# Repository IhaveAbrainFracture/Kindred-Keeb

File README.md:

# Kindred-Keeb
A keyboard themed and designed around the league of legends character Kindred, made for a certain someone <3

# why i made this
So the chronic ado fan this is going to is a keyboard fan and arguably a nerd in all things keyboard related and im not, this project was in part 1. to make a rly good gift but even more 2. to understand keyboards (the in's and the out's) such that when she eventually starts rambling again i can understand all the keyboard things she spews out.

View the full cad here (open in a new tab) : https://cad.onshape.com/documents/49660f55174e9c1ee612018b/w/865d86d8a66051a73309fb28/e/2b79c125cb158cfc9eb8a47f?renderMode=0&leftPanel=false&uiState=687a42a20f797b40055a065f

# Specificaton (Firmware)
1. 3 LAYERS OF FULL CUSTOMISABILITY!!!!!
2. 5 intergrated macros
3. kmk and fully open source

# Specifications (Electronics)
1. Hot swappable (you dont need to get married to the first switch you solder)
2. cool silk layer
3. run by a pico

# Specifications (Mechanical)
1. minimal bolts and others
2. textured arm rest that is magnetically held
3. only 4 major printed parts
4. custom keycaps
5. very thematicaly/lore accurate

# instructions to build
1.using the dowels and such attach the 2 major case and plate parts together then if possible 'melt' then together (like press a iron on both or smthing)

2. in the allocated area insert the insert nuts
   
3.cut and place the foam in the alloacted area then place the pcb on the groves outlines for it

4. place the fully assembled plate ontop of the pcb before placing all the switches
   
5. place the plate pcb sandwitch on the case and bolt into the allocated bolt holes and pray

# BOM 
| Item | Amount | Cost (AUD) | Cost (USD) | Link |
|------|--------|--------------|------------|------|
|Magnets| 50 (i cant order less)  |   $3.32      |        .. | [here](https://www.aliexpress.com/item/1005009515673951.html?spm=a2g0o.productlist.main.3.924e5032RkWiGB&algo_pvid=626def4a-fc6e-4400-b7f1-f96717275f47&algo_exp_id=626def4a-fc6e-4400-b7f1-f96717275f47-2&pdp_ext_f=%7B"order"%3A"-1"%2C"eval"%3A"1"%7D&pdp_npi=4%40dis%21AUD%215.35%213.32%21%21%213.43%212.13%21%402101c5bf17528901380865997ea1e8%2112000049339085641%21sea%21AU%216189345413%21X&curPageLogUid=kPWgozpKm8qq&utparam-url=scene%3Asearch%7Cquery_from%3A)     |
| Stabilisers|  1x   |   9.69           |            |   [Here](https://www.aliexpress.com/item/1005009309795353.html?spm=a2g0o.cart.0.0.75b938dasyPdvw&mp=1&pdp_npi=5%40dis%21AUD%21AUD%2017.62%21AUD%209.69%21%21AUD%209.69%21%21%21%4021010c9a17528903143906876e5d89%2112000048700927954%21ct%21AU%216189345413%21%211%210)   |
|   Akko blue switches   |   45x     |    23.19          |            |   [here](https://www.aliexpress.com/item/1005005514262670.html?spm=a2g0o.cart.0.0.75b938dasyPdvw&mp=1&pdp_npi=5%40dis%21AUD%21AUD%2027.28%21AUD%2023.19%21%21AUD%2023.19%21%21%21%4021010c9a17528903143906876e5d89%2112000033372141692%21ct%21AU%216189345413%21%211%210&pdp_ext_f=%7B"cart2PdpParams"%3A%7B"pdpBusinessMode"%3A"retail"%7D%7D)   |
| Keycaps 132 key purple  |   1x    |     20.61         |            |   [here](https://www.aliexpress.com/item/1005004537134105.html?spm=a2g0o.cart.0.0.3c6e38daAxo2kM&mp=1&pdp_npi=5%40dis%21AUD%21AUD%2032.75%21AUD%2020.61%21%21AUD%2020.61%21%21%21%402140c1e917528955492384666e3753%2112000048938905559%21ct%21AU%216189345413%21%211%210)   |
|  Raspberry pi pico    |   1x     |    2.84          |            |   [here](https://www.aliexpress.com/item/1005008478649106.html?spm=a2g0o.cart.0.0.3c6e38daAxo2kM&mp=1&pdp_npi=5%40dis%21AUD%21AUD%205.67%21AUD%202.84%21%21AUD%202.84%21%21%21%402140c1e917528955456844572e3753%2112000045323954583%21ct%21AU%216189345413%21%211%210)   |
|    50 m2 bolts|     1x   |        2.29      |            |     [here](https://www.aliexpress.com/item/32810872544.html?spm=a2g0o.cart.0.0.3c6e38daAxo2kM&mp=1&pdp_npi=5%40dis%21AUD%21AUD%202.42%21AUD%202.29%21%21AUD%202.29%21%21%21%402140c1e917528955456844572e3753%2112000037536050521%21ct%21AU%216189345413%21%211%210) |
|    50x 3.2 od m2 insert nut  |   x1     |         2.29     |            |  [here](https://www.aliexpress.com/item/1005008666672949.html?spm=a2g0o.cart.0.0.3c6e38daAxo2kM&mp=1&pdp_npi=5%40dis%21AUD%21AUD%202.53%21AUD%202.19%21%21AUD%202.19%21%21%21%402140c1e917528955456844572e3753%2112000046157335265%21ct%21AU%216189345413%21%211%210)    |
|    100x n4148 diodes  |    x1    |    2.79       |            |  [here](https://www.aliexpress.com/item/4000142272546.html?spm=a2g0o.cart.0.0.3c6e38daAxo2kM&mp=1&pdp_npi=5%40dis%21AUD%21AUD%202.88%21AUD%202.79%21%21AUD%202.79%21%21%21%402140c1e917528955456844572e3753%2110000000428321629%21ct%21AU%216189345413%21%211%210)    |
|  desoldering braid wick     |    x1    |     4.43         |            | [here](https://www.aliexpress.com/item/1005006427770026.html?spm=a2g0o.cart.0.0.3c6e38daAxo2kM&mp=1&pdp_npi=5%40dis%21AUD%21AUD%204.60%21AUD%204.43%21%21AUD%204.43%21%21%21%402140c1e917528955456844572e3753%2112000040050106341%21ct%21AU%216189345413%21%211%210)     |
|    Akko purple switch  |   45x     |  25.59            |            |   [here](https://www.aliexpress.com/item/1005007551750020.html?spm=a2g0o.cart.0.0.3c6e38daAxo2kM&mp=1&pdp_npi=5%40dis%21AUD%21AUD%2026.60%21AUD%2025.59%21%21AUD%2025.59%21%21%21%402140c1e917528955456844572e3753%2112000041261720392%21ct%21AU%216189345413%21%211%210)   |
| kailh hot swap socket     |   70x     |       5.54       |            |  [here](https://www.aliexpress.com/item/1005007225352311.html?spm=a2g0o.cart.0.0.3c6e38daAxo2kM&mp=1&pdp_npi=5%40dis%21AUD%21AUD%2014.81%21AUD%205.54%21%21AUD%205.54%21%21%21%402140c1e917528955456844572e3753%2112000039872158641%21ct%21AU%216189345413%21%211%210)    |
|   2mm thick eva foam  |   1x   |      4.79      |            |    [here](https://www.aliexpress.com/item/1005009318717019.html?spm=a2g0o.cart.0.0.3c6e38daAxo2kM&mp=1&pdp_npi=5%40dis%21AUD%21AUD%209.54%21AUD%204.79%21%21AUD%204.79%21%21%21%402140c1e917528955456844572e3753%2112000048733157950%21ct%21AU%216189345413%21%211%210)  |
|  silent lemon v3 switch  |  10x  |  4.86            |            |    [here](https://www.aliexpress.com/item/1005007459638140.html?spm=a2g0o.cart.0.0.3c6e38daAxo2kM&mp=1&pdp_npi=5%40dis%21AUD%21AUD%2013.57%21AUD%209.18%21%21AUD%209.18%21%21%21%402140c1e917528955456844572e3753%2112000040861161458%21ct%21AU%216189345413%21%211%21)  |
|   PCB   |   5x     |   59.86           |            |   
  |
|  3D Printing   |   a lot     |     Free         |            |   Printing legion   |

Total: 

AUD: 181.82 (WITH SHIPPING)

USD:118.84 (WITH SHIPPING)

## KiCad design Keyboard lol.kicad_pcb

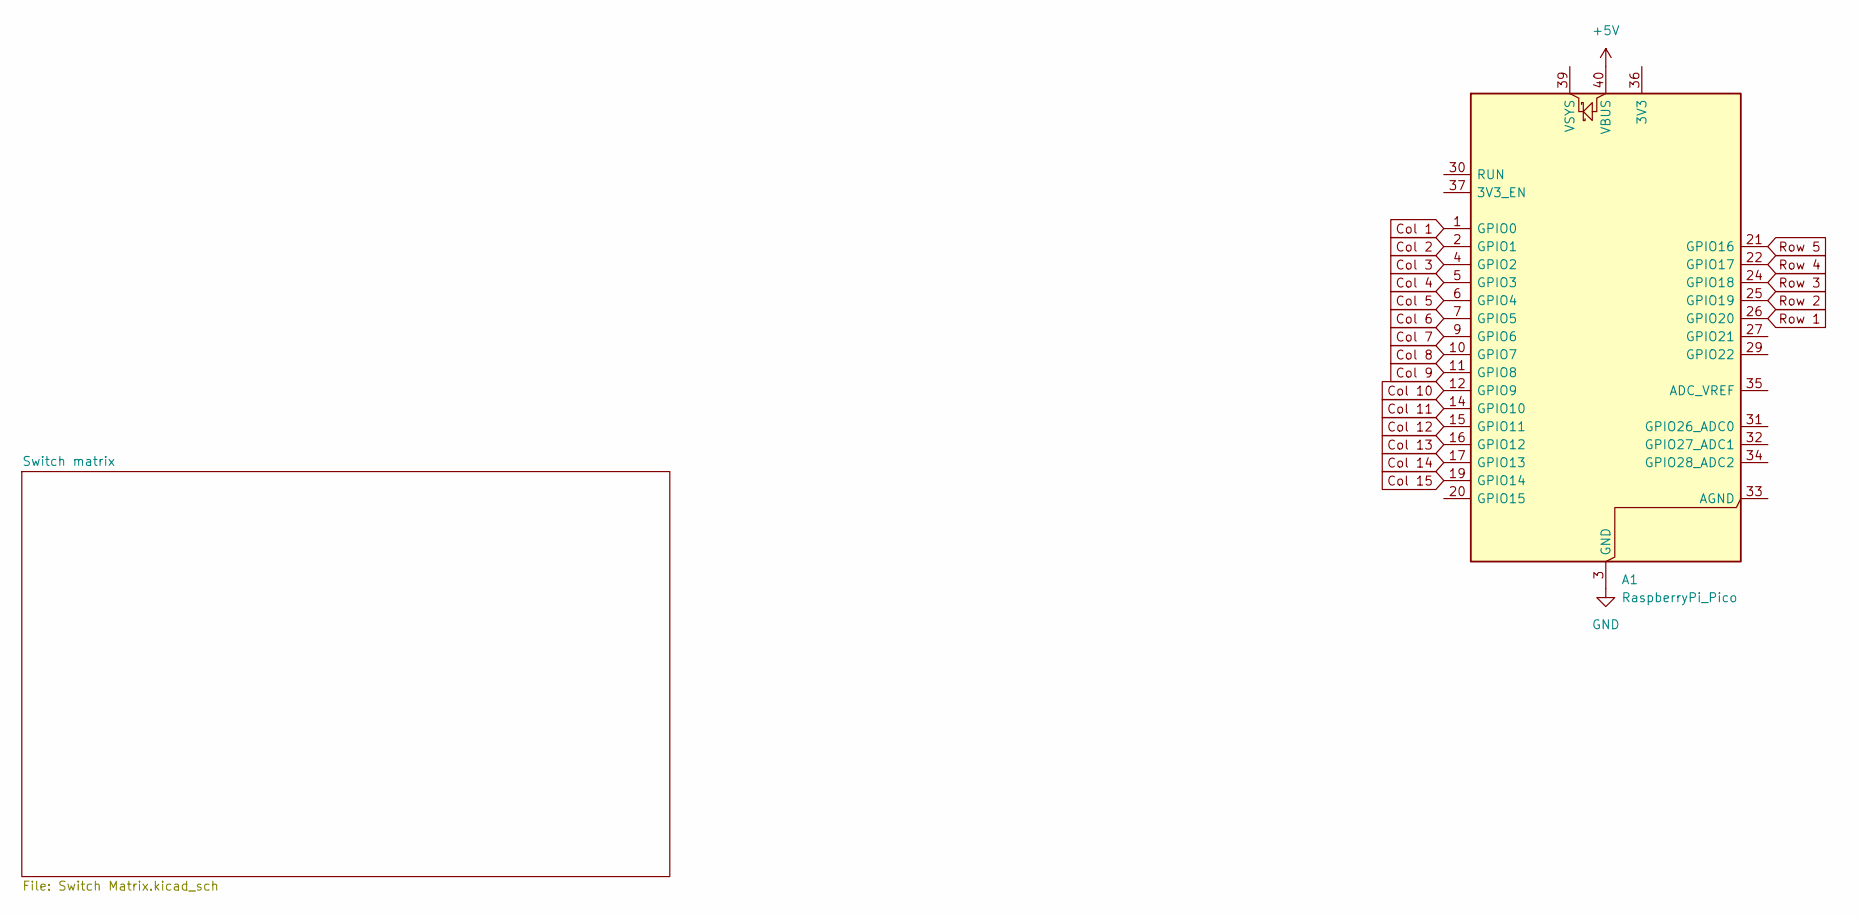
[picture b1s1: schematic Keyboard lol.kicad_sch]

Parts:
A1: RaspberryPi_Pico; RaspberryPi_Pico_Common_THT

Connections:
+5V: A1.40 (VBUS)
Col 1: A1.1 (GPIO0); also elsewhere on the board
Col 2: A1.2 (GPIO1); also elsewhere on the board
Col 3: A1.4 (GPIO2); also elsewhere on the board
Col 4: A1.5 (GPIO3); also elsewhere on the board
Col 5: A1.6 (GPIO4); also elsewhere on the board
Col 6: A1.7 (GPIO5); also elsewhere on the board
Col 7: A1.9 (GPIO6); also elsewhere on the board
Col 8: A1.10 (GPIO7); also elsewhere on the board
Col 9: A1.11 (GPIO8); also elsewhere on the board
Col 10: A1.12 (GPIO9); also elsewhere on the board
Col 11: A1.14 (GPIO10); also elsewhere on the board
Col 12: A1.15 (GPIO11); also elsewhere on the board
Col 13: A1.16 (GPIO12); also elsewhere on the board
Col 14: A1.17 (GPIO13); also elsewhere on the board
GND: A1.3 (GND), A1.8 (GND), A1.13 (GND), A1.18 (GND), A1.23 (GND), A1.28 (GND), A1.38 (GND)
Row 1: A1.26 (GPIO20); also elsewhere on the board
Row 2: A1.25 (GPIO19); also elsewhere on the board
Row 3: A1.24 (GPIO18); also elsewhere on the board
Row 4: A1.22 (GPIO17); also elsewhere on the board
Row 5: A1.21 (GPIO16); also elsewhere on the board

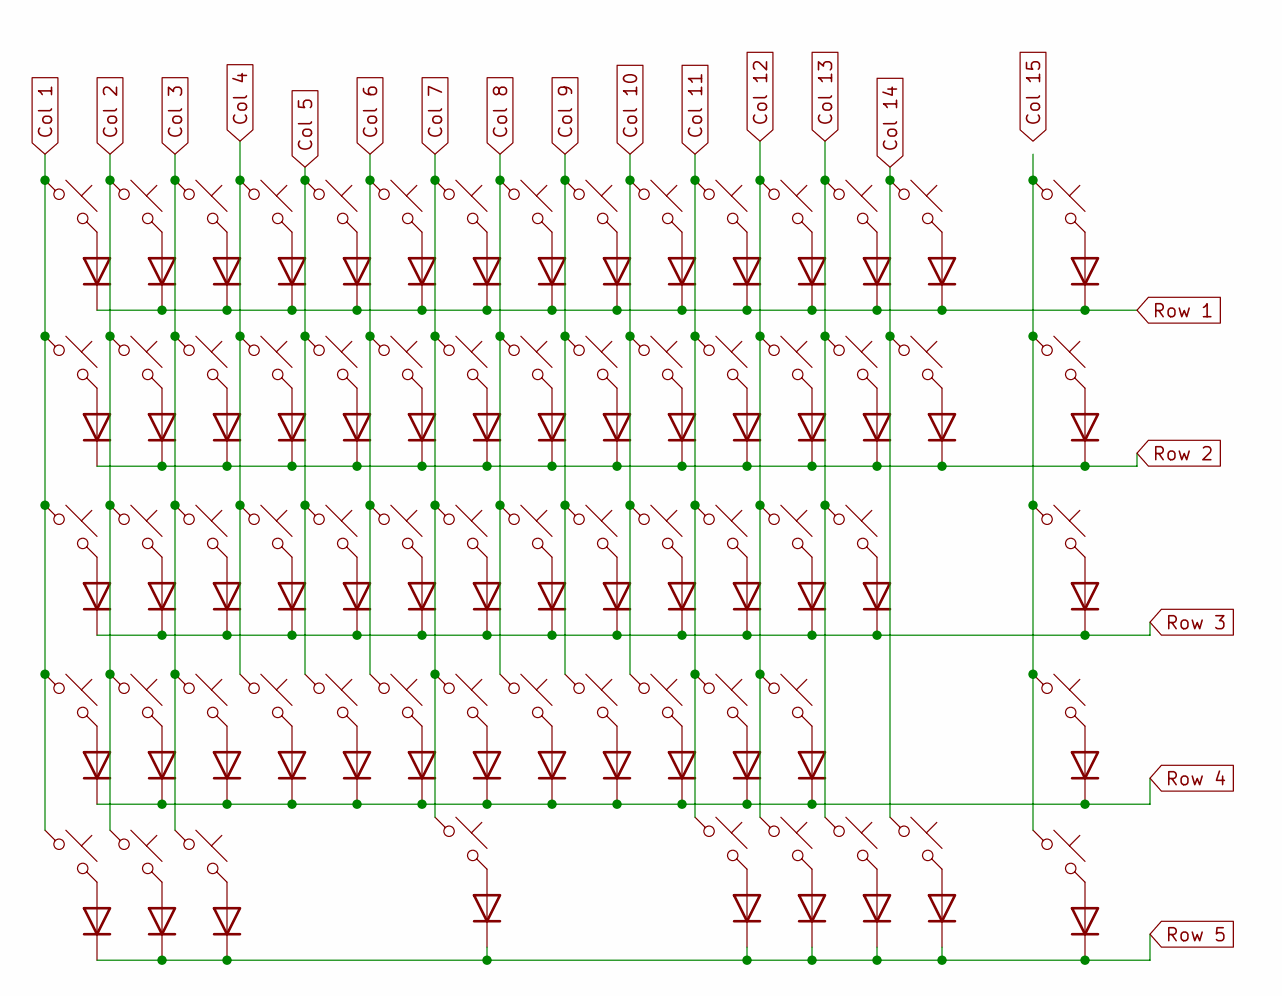
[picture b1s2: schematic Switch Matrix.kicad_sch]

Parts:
D1, D2, D3, D4, D5, D6, D7, D8, D9, D10, D11, D12, D13, D14, D15, D16, D17, D18, D19, D20, D21, D22, D23, D24, D25, D26, D27, D28, D30, D31, D32, D33, D34, D35, D36, D37, D38, D39, D40, D41, D42, D45, D46, D47, D48, D49, D50, D51, D52, D53, D54, D55, D56, D57, D58, D59, D60, D61, D62, D63, D64, D65, D66, D67, D68, D75: 1N4148; D_DO-35_SOD27_P7.62mm_Horizontal
SW1, SW14: SW_Push_45deg; MX-Hotswap-1.5U
SW2, SW3, SW4, SW5, SW6, SW7, SW8, SW9, SW10, SW11, SW12, SW13, SW15, SW17, SW18, SW19, SW20, SW21, SW22, SW23, SW24, SW25, SW26, SW27, SW30, SW32, SW33, SW34, SW35, SW36, SW37, SW38, SW39, SW40, SW41, SW45, SW46, SW47, SW48, SW49, SW50, SW51, SW52, SW53, SW54, SW55, SW56, SW57, SW58, SW60, SW75: SW_Push_45deg; MX-Hotswap-1U
SW16: SW_Push_45deg; MX-Hotswap-1.75U
SW28, SW31: SW_Push_45deg; MX-Hotswap-2.25U
SW42: SW_Push_45deg; MX-Hotswap-2.75U
SW59: SW_Push_45deg; MX-Hotswap-2U
SW61, SW62, SW63, SW65, SW66, SW67, SW68: SW_Push_45deg; MX-Hotswap-1.25U
SW64: SW_Push_45deg; MX-Hotswap-6.25U-ReversedStabilizers

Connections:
Col 1: SW1.1, SW16.1, SW31.1, SW46.1, SW61.1; also elsewhere on the board
Col 2: SW2.1, SW17.1, SW32.1, SW47.1, SW62.1; also elsewhere on the board
Col 3: SW3.1, SW18.1, SW33.1, SW48.1, SW63.1; also elsewhere on the board
Col 4: SW4.1, SW19.1, SW34.1, SW49.1; also elsewhere on the board
Col 5: SW5.1, SW20.1, SW35.1, SW50.1; also elsewhere on the board
Col 6: SW6.1, SW21.1, SW36.1, SW51.1; also elsewhere on the board
Col 7: SW7.1, SW22.1, SW37.1, SW52.1, SW64.1; also elsewhere on the board
Col 8: SW8.1, SW23.1, SW38.1, SW53.1; also elsewhere on the board
Col 9: SW9.1, SW24.1, SW39.1, SW54.1; also elsewhere on the board
Col 10: SW10.1, SW25.1, SW40.1, SW55.1; also elsewhere on the board
Col 11: SW11.1, SW26.1, SW41.1, SW56.1, SW65.1; also elsewhere on the board
Col 12: SW12.1, SW27.1, SW42.1, SW57.1, SW66.1; also elsewhere on the board
Col 13: SW13.1, SW28.1, SW58.1, SW67.1; also elsewhere on the board
Col 14: SW14.1, SW59.1, SW68.1; also elsewhere on the board
unnamed: D1.2 (A), SW1.2
unnamed: D2.2 (A), SW2.2
unnamed: D3.2 (A), SW3.2
unnamed: D4.2 (A), SW4.2
unnamed: D5.2 (A), SW5.2
unnamed: D6.2 (A), SW6.2
unnamed: D7.2 (A), SW7.2
unnamed: D8.2 (A), SW8.2
unnamed: D9.2 (A), SW9.2
unnamed: D10.2 (A), SW10.2
unnamed: D11.2 (A), SW11.2
unnamed: D12.2 (A), SW12.2
unnamed: D13.2 (A), SW13.2
unnamed: D14.2 (A), SW14.2
unnamed: D15.2 (A), SW15.2
unnamed: D16.2 (A), SW16.2
unnamed: D17.2 (A), SW17.2
unnamed: D18.2 (A), SW18.2
unnamed: D19.2 (A), SW19.2
unnamed: D20.2 (A), SW20.2
unnamed: D21.2 (A), SW21.2
unnamed: D22.2 (A), SW22.2
unnamed: D23.2 (A), SW23.2
unnamed: D24.2 (A), SW24.2
unnamed: D25.2 (A), SW25.2
unnamed: D26.2 (A), SW26.2
unnamed: D27.2 (A), SW27.2
unnamed: D28.2 (A), SW28.2
unnamed: D30.2 (A), SW30.2
unnamed: D31.2 (A), SW31.2
unnamed: D32.2 (A), SW32.2
unnamed: D33.2 (A), SW33.2
unnamed: D34.2 (A), SW34.2
unnamed: D35.2 (A), SW35.2
unnamed: D36.2 (A), SW36.2
unnamed: D37.2 (A), SW37.2
unnamed: D38.2 (A), SW38.2
unnamed: D39.2 (A), SW39.2
unnamed: D40.2 (A), SW40.2
unnamed: D41.2 (A), SW41.2
unnamed: D42.2 (A), SW42.2
unnamed: D45.2 (A), SW45.2
unnamed: D46.2 (A), SW46.2
unnamed: D47.2 (A), SW47.2
unnamed: D48.2 (A), SW48.2
unnamed: D49.2 (A), SW49.2
unnamed: D50.2 (A), SW50.2
unnamed: D51.2 (A), SW51.2
unnamed: D52.2 (A), SW52.2
unnamed: D53.2 (A), SW53.2
unnamed: D54.2 (A), SW54.2
unnamed: D55.2 (A), SW55.2
unnamed: D56.2 (A), SW56.2
unnamed: D57.2 (A), SW57.2
unnamed: D58.2 (A), SW58.2
unnamed: D59.2 (A), SW59.2
unnamed: D60.2 (A), SW60.2
unnamed: D61.2 (A), SW61.2
unnamed: D62.2 (A), SW62.2
unnamed: D63.2 (A), SW63.2
unnamed: D64.2 (A), SW64.2
unnamed: D65.2 (A), SW65.2
unnamed: D66.2 (A), SW66.2
unnamed: D67.2 (A), SW67.2
unnamed: D68.2 (A), SW68.2
unnamed: D75.2 (A), SW75.2
Row 1: D46.1 (K), D47.1 (K), D48.1 (K), D49.1 (K), D50.1 (K), D51.1 (K), D52.1 (K), D53.1 (K), D54.1 (K), D55.1 (K), D56.1 (K), D57.1 (K), D58.1 (K), D59.1 (K), D60.1 (K); also elsewhere on the board
Row 2: D1.1 (K), D2.1 (K), D3.1 (K), D4.1 (K), D5.1 (K), D6.1 (K), D7.1 (K), D8.1 (K), D9.1 (K), D10.1 (K), D11.1 (K), D12.1 (K), D13.1 (K), D14.1 (K), D15.1 (K); also elsewhere on the board
Row 3: D16.1 (K), D17.1 (K), D18.1 (K), D19.1 (K), D20.1 (K), D21.1 (K), D22.1 (K), D23.1 (K), D24.1 (K), D25.1 (K), D26.1 (K), D27.1 (K), D28.1 (K), D30.1 (K); also elsewhere on the board
Row 4: D31.1 (K), D32.1 (K), D33.1 (K), D34.1 (K), D35.1 (K), D36.1 (K), D37.1 (K), D38.1 (K), D39.1 (K), D40.1 (K), D41.1 (K), D42.1 (K), D45.1 (K); also elsewhere on the board
Row 5: D61.1 (K), D62.1 (K), D63.1 (K), D64.1 (K), D65.1 (K), D66.1 (K), D67.1 (K), D68.1 (K), D75.1 (K); also elsewhere on the board

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
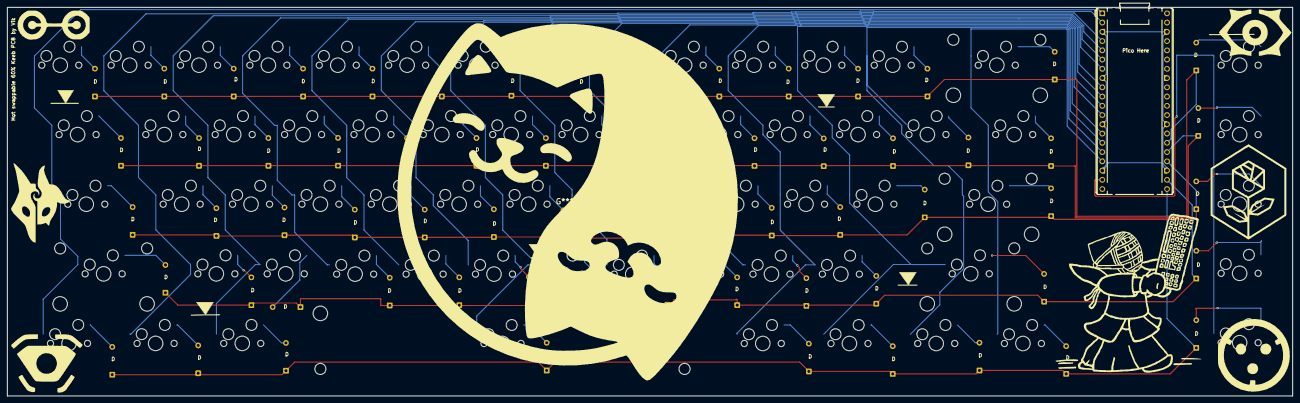
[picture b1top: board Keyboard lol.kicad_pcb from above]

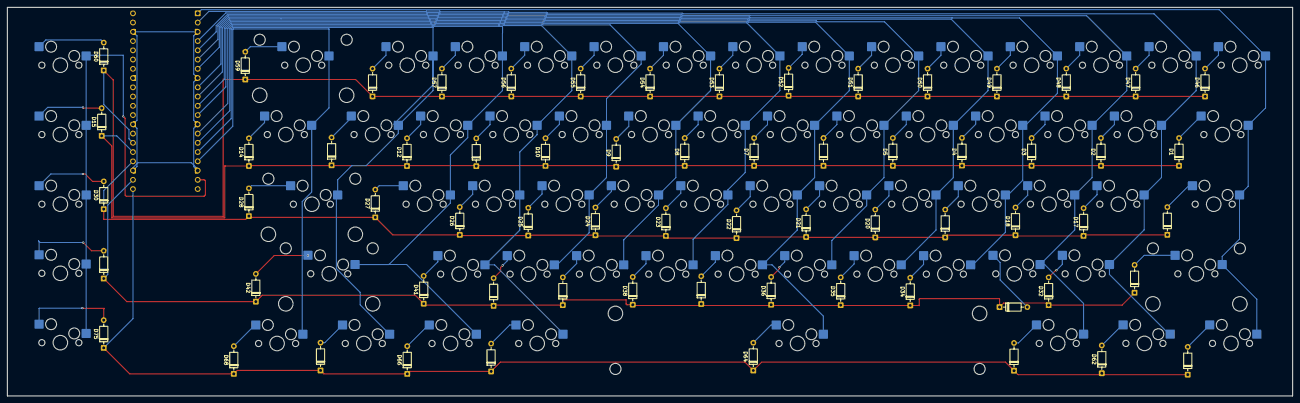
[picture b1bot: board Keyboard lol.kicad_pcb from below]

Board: 2 copper layers, 352.9 x 106.7 mm, 133 parts (132 on the bottom side), 87 nets.

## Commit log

2025-07-15 Create Journal.md
    filled in journal for the days i procastinated
2025-07-18 full journal overhaul
2025-07-18 cleaned and finished
2025-07-18 Read me isnt dead anymore
2025-07-18 FIRMWARE
    Everything that needs to be flashed onto your pico
2025-07-18 Added Manufacturing files
2025-07-18 All relvent Kicad files
2025-07-18 All cad files
2025-07-18 Re-orering
2025-07-19 RENAMED
2025-07-26 file
2025-07-26 help
